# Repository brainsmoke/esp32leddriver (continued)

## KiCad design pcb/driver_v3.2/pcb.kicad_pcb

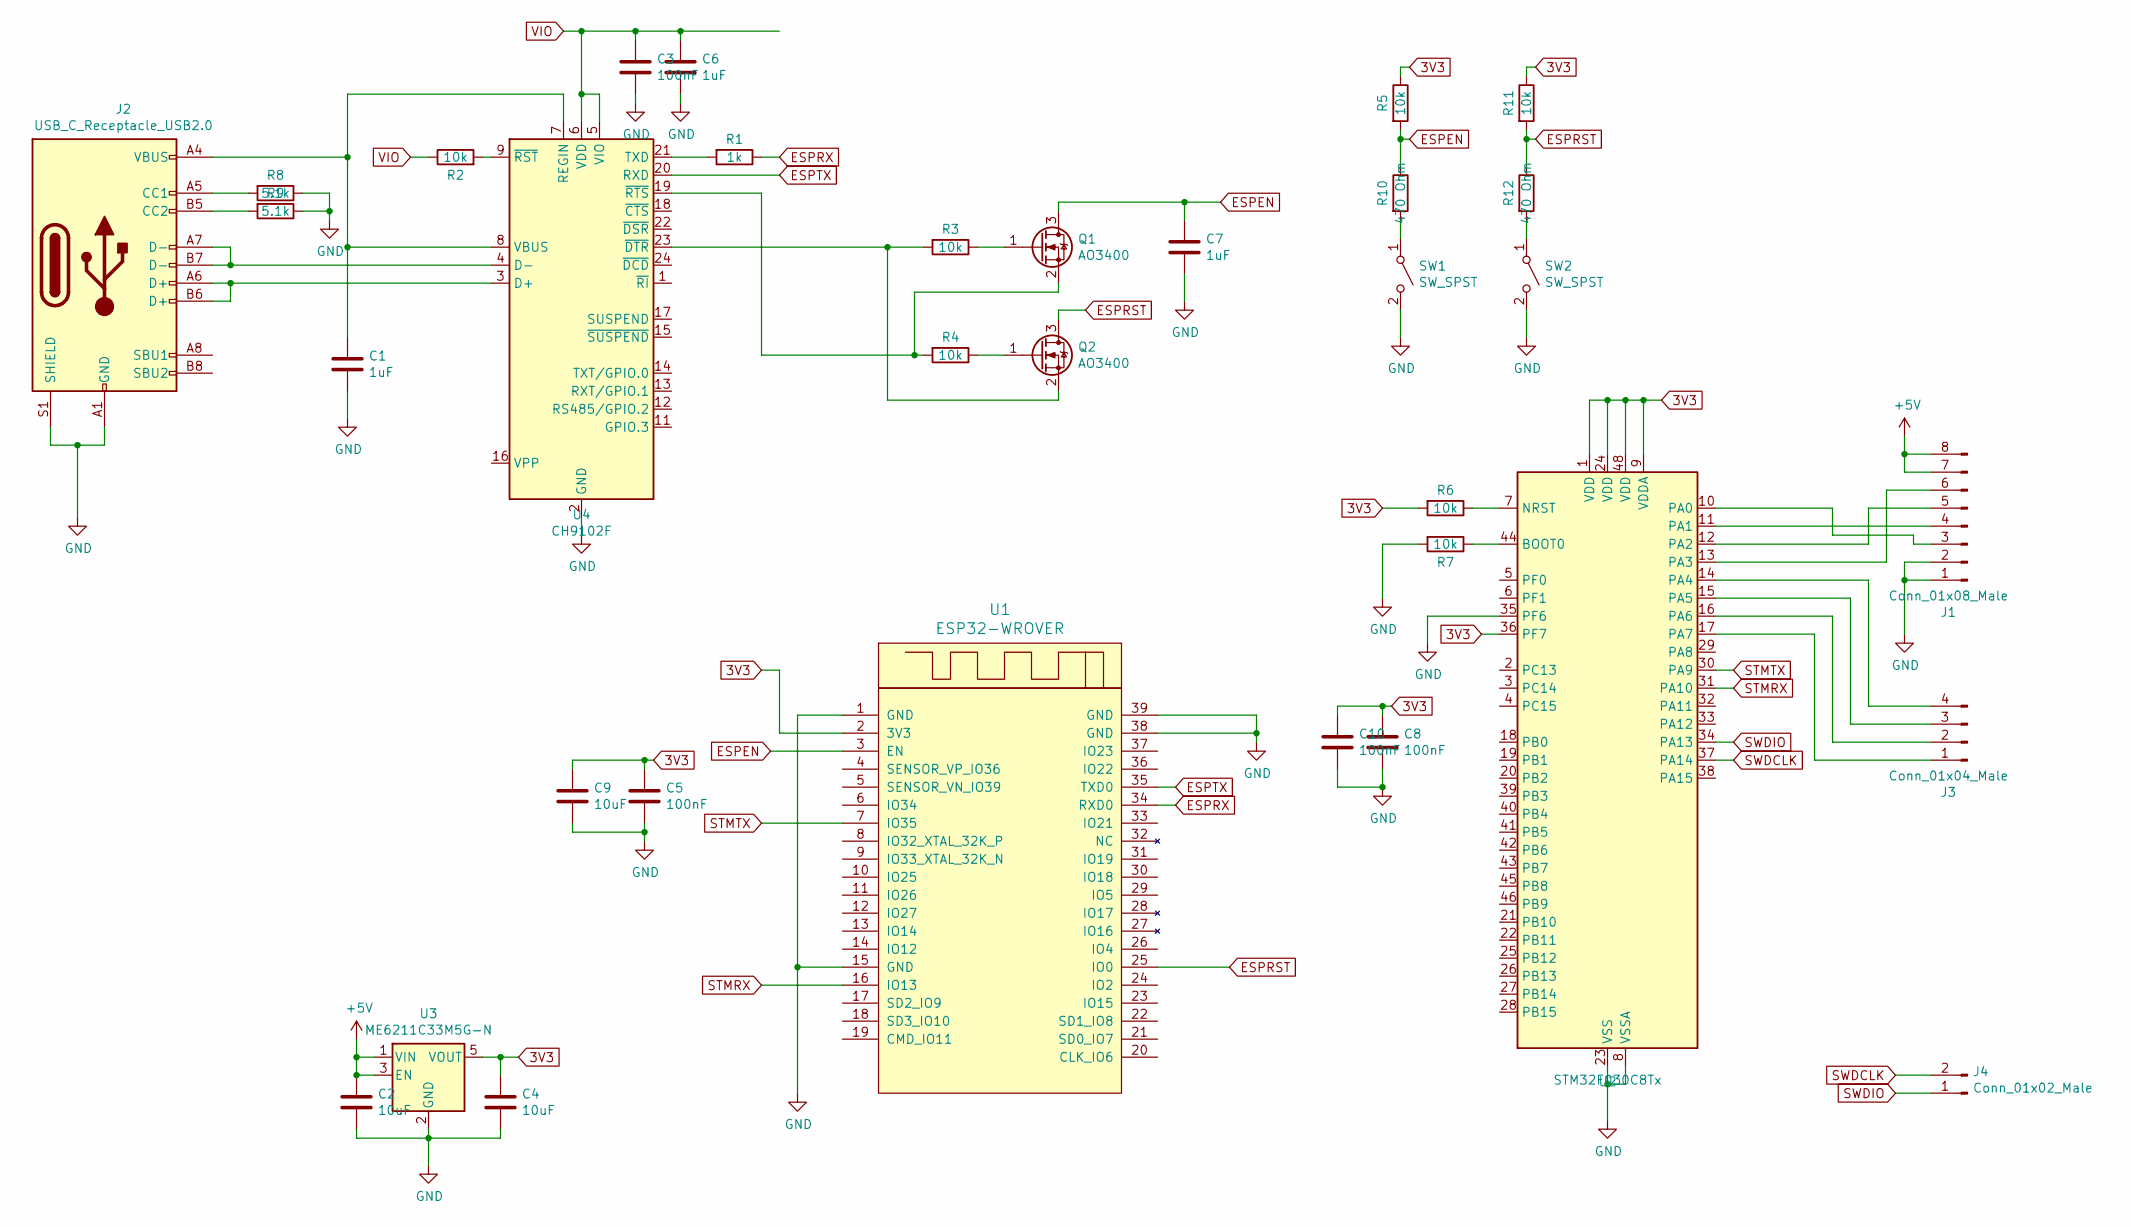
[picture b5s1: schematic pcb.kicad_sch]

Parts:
C1, C6, C7: 1uF; C_0402_1005Metric; LCSC C52923
C2, C4, C9: 10uF; C_0603_1608Metric; LCSC C19702
C3, C5, C8, C10: 100nF; C_0402_1005Metric; LCSC C1525
J1: Conn_01x08_Male; PinHeader_1x08_P2.54mm_Vertical
J2: USB_C_Receptacle_USB2.0; USB_C_Receptacle_HRO_TYPE-C-31-M-12; LCSC C165948
J3: Conn_01x04_Male; PinHeader_1x04_P2.54mm_Vertical
J4: Conn_01x02_Male; PinHeader_1x02_P2.54mm_Vertical
Q1, Q2: AO3400; SOT-23; LCSC C20917
R1: 1k; R_0402_1005Metric; LCSC C11702
R2, R3, R4, R5, R6, R7, R11: 10k; R_0402_1005Metric; LCSC C25744
R8, R9: 5.1k; R_0402_1005Metric; LCSC C25905
R10, R12: 470 Ohm; R_0402_1005Metric; LCSC C25117
SW1, SW2: SW_SPST; SW_Push_1P1T_NO_CK_KMR2; LCSC C318893
U1: ESP32-WROVER; XCVR_ESP32-WROVER
U2: STM32F030C8Tx; LQFP-48_7x7mm_P0.5mm; LCSC C23922
U3: ME6211C33M5G-N; SOT-23-5; LCSC C82942
U4: CH9102F; QFN-24-1EP_4x4mm_P0.5mm_EP2.6x2.6mm; LCSC C2858418

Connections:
3V3: C4.1, C5.1, C8.1, C9.1, C10.1, R5.1, R6.2, R11.1, U1.2 (3V3), U2.1 (VDD), U2.9 (VDDA), U2.24 (VDD), U2.36 (PF7), U2.48 (VDD), U3.5 (VOUT)
+5V: C2.1, J1.7, J1.8, U3.1 (VIN), U3.3 (EN)
ESPEN: C7.1, Q1.3 (D), R5.2, R10.1, U1.3 (EN)
ESPRST: Q2.3 (D), R11.2, R12.1, U1.25 (IO0)
ESPRX: R1.1, U1.34 (RXD0)
ESPTX: U1.35 (TXD0), U4.20 (RXD)
GND: C1.2, C2.2, C3.2, C4.2, C5.2, C6.2, C7.2, C8.2, C9.2, C10.2, J1.1, J1.2, J2.A1 (GND), J2.A12 (GND), J2.B1 (GND), J2.B12 (GND), J2.S1 (SHIELD), R7.2, R8.1, R9.1, SW1.2 (B), SW2.2 (B), U1.1 (GND), U1.15 (GND), U1.38 (GND), U1.39 (GND), U2.8 (VSSA), U2.23 (VSS), U2.35 (PF6), U2.47 (VSS), U3.2 (GND), U4.2 (GND), U4.25 (GND)
unnamed: J1.3, U2.10 (PA0)
unnamed: J1.4, U2.11 (PA1)
unnamed: J1.5, U2.12 (PA2)
unnamed: J1.6, U2.13 (PA3)
unnamed: J2.A5 (CC1), R8.2
unnamed: J2.B5 (CC2), R9.2
unnamed: J3.1, U2.17 (PA7)
unnamed: J3.2, U2.16 (PA6)
unnamed: J3.3, U2.15 (PA5)
unnamed: J3.4, U2.14 (PA4)
unnamed: Q1.1 (G), R3.1
unnamed: Q1.2 (S), R4.2, U4.19 (~RTS)
unnamed: Q2.1 (G), R4.1
unnamed: Q2.2 (S), R3.2, U4.23 (~DTR)
unnamed: R10.2, SW1.1 (A)
unnamed: R12.2, SW2.1 (A)
unnamed: R7.1, U2.44 (BOOT0)
unnamed: R6.1, U2.7 (NRST)
unnamed: J2.A6 (D+), J2.B6 (D+), U4.3 (D+)
unnamed: J2.A7 (D-), J2.B7 (D-), U4.4 (D-)
unnamed: C1.1, J2.A4 (VBUS), J2.A9 (VBUS), J2.B4 (VBUS), J2.B9 (VBUS), U4.7 (REGIN), U4.8 (VBUS)
unnamed: R1.2, U4.21 (TXD)
unnamed: R2.2, U4.9 (~RST)
STMRX: U1.16 (IO13), U2.31 (PA10)
STMTX: U1.7 (IO35), U2.30 (PA9)
SWDCLK: J4.2, U2.37 (PA14)
SWDIO: J4.1, U2.34 (PA13)
VIO: C3.1, C6.1, R2.1, U4.5 (VIO), U4.6 (VDD)

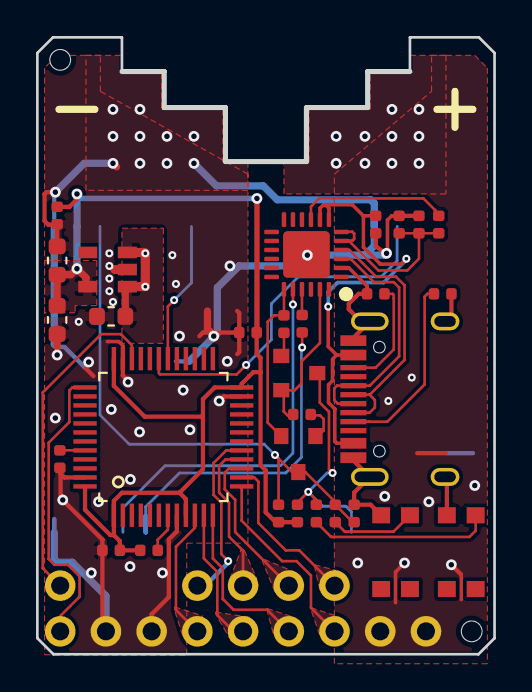
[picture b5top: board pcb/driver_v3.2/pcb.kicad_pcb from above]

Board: 4 copper layers, 25.4 x 34.3 mm, 34 parts (1 on the bottom side), 35 nets.

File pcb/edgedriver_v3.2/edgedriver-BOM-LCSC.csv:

Comment,Designator,Footprint,LCSC Part Number
"10uF","C4,C2,C9","0603","C19702"
"1uF","C7,C6,C1","0402","C52923"
"100nF","C8,C5,C3,C10","0402","C1525"
"USB_C_Receptacle_USB2.0","J2","TYPE-C-31_L8.94_W7.3","C165948"
"AO3400","Q1,Q2","SOT-23-3L","C20917"
"1k","R1","0402","C11702"
"470 Ohm","R10,R12","0402","C25167"
"10k","R6,R7,R3,R4,R5,R2,R11","0402","C25744"
"5.1k","R8,R9","0402","C25905"
"SW_SPST","SW1,SW2","Button_Switch_SMD:SW_Push_1P1T_NO_CK_KMR2","C318893"
"STM32F030C8T6","U2","LQFP-48_7.0x7.0x0.5P","C23922"
"AMS1117-3.3","U3","SOT-223","C6186"
"CH9102F","U4","QFN-24_L4.0-W4.0-P0.50EP2.8","C2858418"

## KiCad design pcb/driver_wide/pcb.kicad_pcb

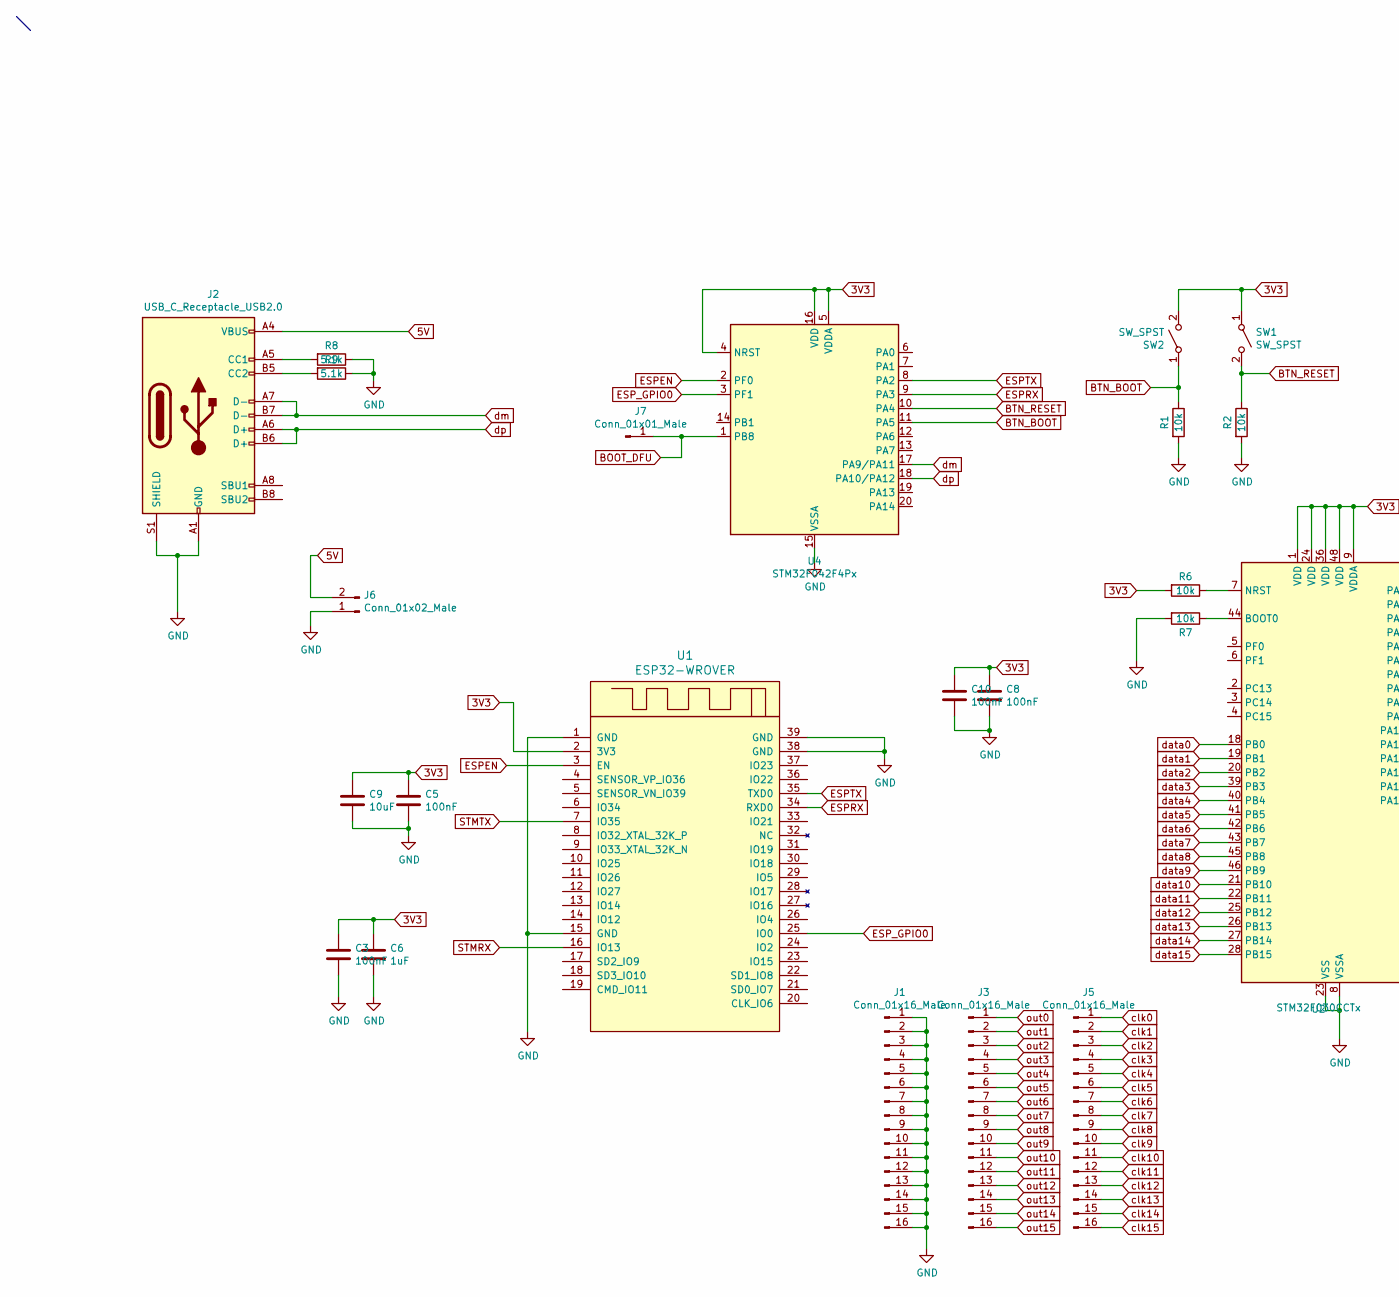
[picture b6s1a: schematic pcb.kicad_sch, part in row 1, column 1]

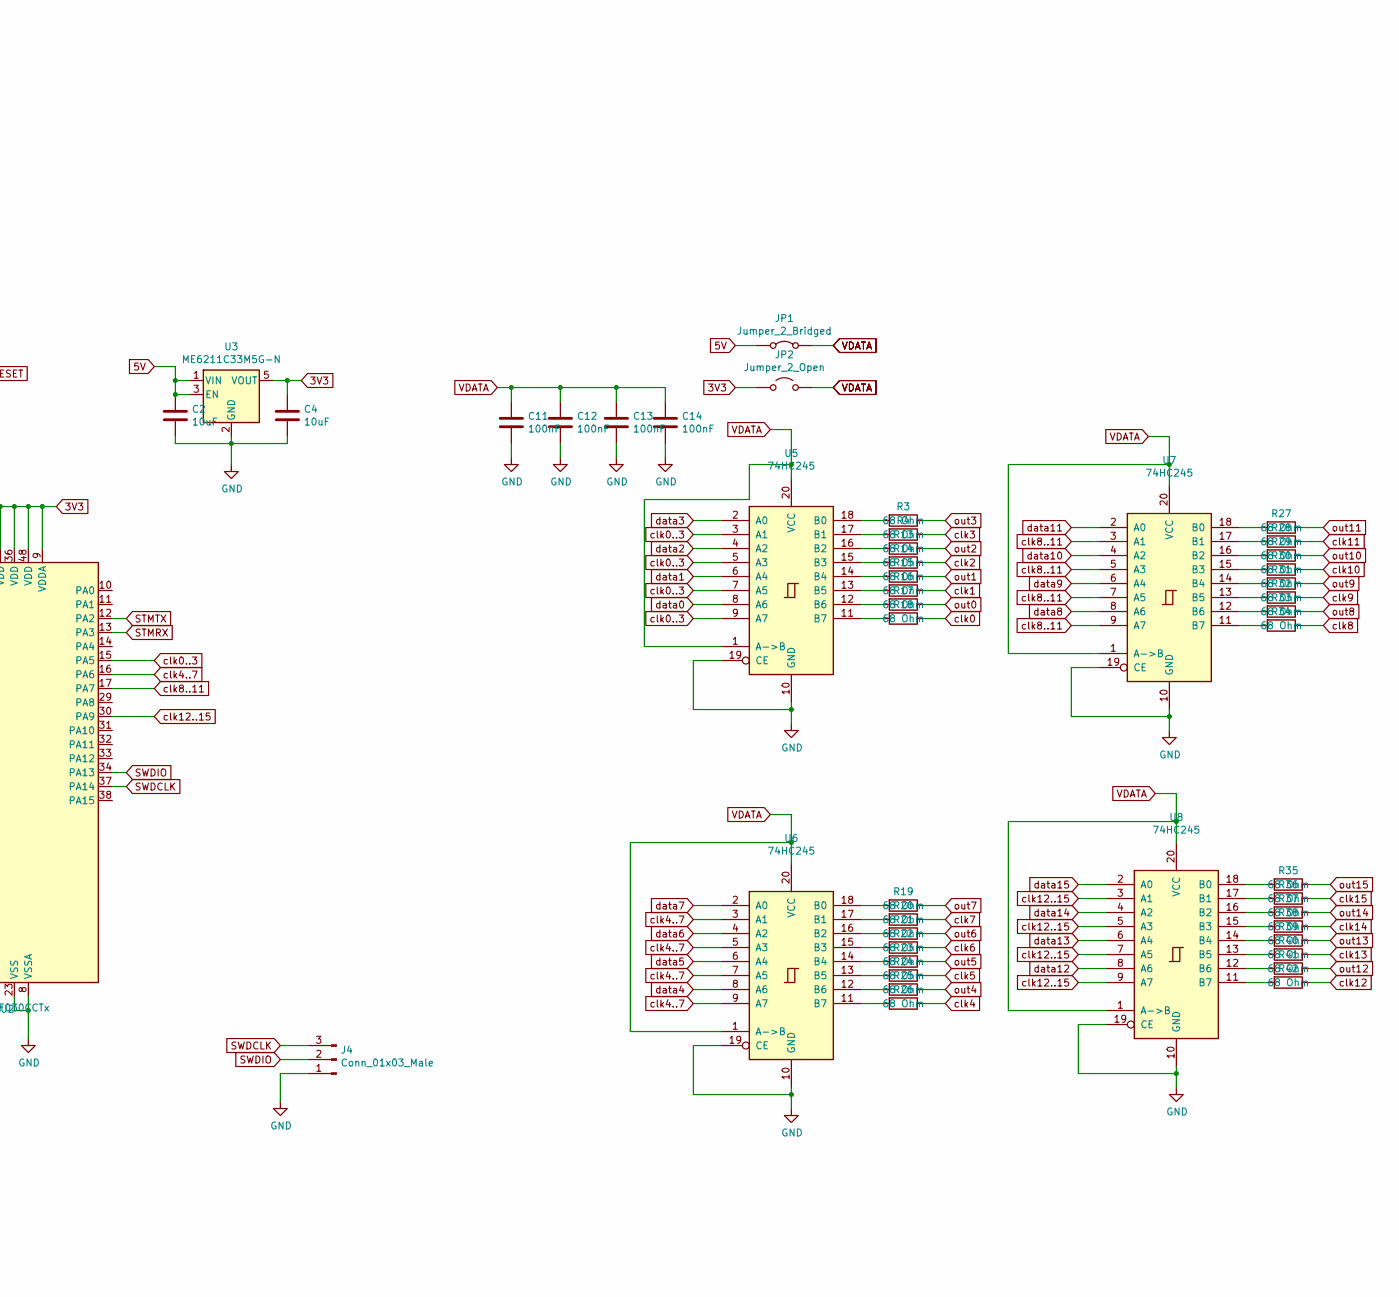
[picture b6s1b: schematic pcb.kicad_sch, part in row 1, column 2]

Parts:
C2, C4, C9: 10uF; C_0603_1608Metric; LCSC C19702
C3, C5, C8, C10: 100nF; C_0402_1005Metric; LCSC C1525
C6: 1uF; C_0402_1005Metric; LCSC C52923
C11, C12, C13, C14: 100nF; C_0402_1005Metric; LCSC C19702
J1, J3, J5: Conn_01x16_Male; PinHeader_1x16_P2.54mm_Vertical
J2: USB_C_Receptacle_USB2.0; USB_C_Receptacle_HRO_TYPE-C-31-M-12; LCSC C165948
J4: Conn_01x03_Male; PinHeader_1x03_P2.54mm_Vertical
J6: Conn_01x02_Male; PinHeader_1x02_P2.54mm_Vertical
J7: Conn_01x01_Male; PinHeader_1x01_P2.54mm_Vertical
JP1: Jumper_2_Bridged; SolderJumper-2_P1.3mm_Bridged_Pad1.0x1.5mm
JP2: Jumper_2_Open; SolderJumper-2_P1.3mm_Open_Pad1.0x1.5mm
R1, R2, R6, R7: 10k; R_0402_1005Metric; LCSC C25744
R3, R4, R13, R14, R15, R16, R17, R18, R19, R20, R21, R22, R23, R24, R25, R26, R27, R28, R29, R30, R31, R32, R33, R34, R35, R36, R37, R38, R39, R40, R41, R42: 68 Ohm; R_0402_1005Metric; LCSC C25744
R8, R9: 5.1k; R_0402_1005Metric; LCSC C25905
SW1, SW2: SW_SPST; SW_Push_1P1T_NO_CK_KMR2; LCSC C318893
U1: ESP32-WROVER; XCVR_ESP32-WROVER
U2: STM32F030CCTx; LQFP-48_7x7mm_P0.5mm
U3: ME6211C33M5G-N; SOT-23-5; LCSC C82942
U4: STM32F042F4Px; TSSOP-20_4.4x6.5mm_P0.65mm
U5, U6, U7, U8: 74HC245; TSSOP-20_4.4x6.5mm_P0.65mm

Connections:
3V3: C3.1, C4.1, C5.1, C6.1, C8.1, C9.1, C10.1, JP2.1 (A), R6.2, SW1.1 (A), SW2.2 (B), U1.2 (3V3), U2.1 (VDD), U2.9 (VDDA), U2.24 (VDD), U2.36 (VDD), U2.48 (VDD), U3.5 (VOUT), U4.4 (NRST), U4.5 (VDDA), U4.16 (VDD)
5V: C2.1, J2.A4 (VBUS), J2.A9 (VBUS), J2.B4 (VBUS), J2.B9 (VBUS), J6.2, JP1.1 (A), U3.1 (VIN), U3.3 (EN)
BOOT_DFU: J7.1, U4.1 (PB8)
BTN_BOOT: R1.1, SW2.1 (A), U4.11 (PA5)
BTN_RESET: R2.1, SW1.2 (B), U4.10 (PA4)
ESPEN: U1.3 (EN), U4.2 (PF0)
ESPRX: U1.34 (RXD0), U4.9 (PA3)
ESPTX: U1.35 (TXD0), U4.8 (PA2)
ESP_GPIO0: U1.25 (IO0), U4.3 (PF1)
GND: C2.2, C3.2, C4.2, C5.2, C6.2, C8.2, C9.2, C10.2, C11.2, C12.2, C13.2, C14.2, J1.1, J1.2, J1.3, J1.4, J1.5, J1.6, J1.7, J1.8, J1.9, J1.10, J1.11, J1.12, J1.13, J1.14, J1.15, J1.16, J2.A1 (GND), J2.A12 (GND), J2.B1 (GND), J2.B12 (GND), J2.S1 (SHIELD), J4.1, J6.1, R1.2, R2.2, R7.2, R8.1, R9.1, U1.1 (GND), U1.15 (GND), U1.38 (GND), U1.39 (GND), U2.8 (VSSA), U2.23 (VSS), U2.35 (VSS), U2.47 (VSS), U3.2 (GND), U4.15 (VSSA), U5.10 (GND), U5.19 (CE), U6.10 (GND), U6.19 (CE), U7.10 (GND), U7.19 (CE), U8.10 (GND), U8.19 (CE)
unnamed: J2.A5 (CC1), R8.2
unnamed: J2.B5 (CC2), R9.2
unnamed: R7.1, U2.44 (BOOT0)
unnamed: R6.1, U2.7 (NRST)
unnamed: R3.2, U5.18 (B0)
unnamed: R4.2, U5.17 (B1)
unnamed: R13.2, U5.16 (B2)
unnamed: R14.2, U5.15 (B3)
unnamed: R15.2, U5.14 (B4)
unnamed: R16.2, U5.13 (B5)
unnamed: R17.2, U5.12 (B6)
unnamed: R18.2, U5.11 (B7)
unnamed: R19.2, U6.18 (B0)
unnamed: R20.2, U6.17 (B1)
unnamed: R21.2, U6.16 (B2)
unnamed: R22.2, U6.15 (B3)
unnamed: R23.2, U6.14 (B4)
unnamed: R24.2, U6.13 (B5)
unnamed: R25.2, U6.12 (B6)
unnamed: R26.2, U6.11 (B7)
unnamed: R27.2, U7.18 (B0)
unnamed: R28.2, U7.17 (B1)
unnamed: R29.2, U7.16 (B2)
unnamed: R30.2, U7.15 (B3)
unnamed: R31.2, U7.14 (B4)
unnamed: R32.2, U7.13 (B5)
unnamed: R33.2, U7.12 (B6)
unnamed: R34.2, U7.11 (B7)
unnamed: R35.2, U8.18 (B0)
unnamed: R36.2, U8.17 (B1)
unnamed: R37.2, U8.16 (B2)
unnamed: R38.2, U8.15 (B3)
unnamed: R39.2, U8.14 (B4)
unnamed: R40.2, U8.13 (B5)
unnamed: R41.2, U8.12 (B6)
unnamed: R42.2, U8.11 (B7)
STMRX: U1.16 (IO13), U2.13 (PA3)
STMTX: U1.7 (IO35), U2.12 (PA2)
SWDCLK: J4.3, U2.37 (PA14)
SWDIO: J4.2, U2.34 (PA13)
VDATA: C11.1, C12.1, C13.1, C14.1, JP1.2 (B), JP2.2 (B), U5.1 (A->B), U5.20 (VCC), U6.1 (A->B), U6.20 (VCC), U7.1 (A->B), U7.20 (VCC), U8.1 (A->B), U8.20 (VCC)
clk0: J5.1, R18.1
clk0..3: U2.15 (PA5), U5.3 (A1), U5.5 (A3), U5.7 (A5), U5.9 (A7)
clk1: J5.2, R16.1
clk2: J5.3, R14.1
clk3: J5.4, R4.1
clk4: J5.5, R26.1
clk4..7: U2.16 (PA6), U6.3 (A1), U6.5 (A3), U6.7 (A5), U6.9 (A7)
clk5: J5.6, R24.1
clk6: J5.7, R22.1
clk7: J5.8, R20.1
clk8: J5.9, R34.1
clk8..11: U2.17 (PA7), U7.3 (A1), U7.5 (A3), U7.7 (A5), U7.9 (A7)
clk9: J5.10, R32.1
clk10: J5.11, R30.1
clk11: J5.12, R28.1
clk12: J5.13, R42.1
clk12..15: U2.30 (PA9), U8.3 (A1), U8.5 (A3), U8.7 (A5), U8.9 (A7)
clk13: J5.14, R40.1
clk14: J5.15, R38.1
clk15: J5.16, R36.1
data0: U2.18 (PB0), U5.8 (A6)
data1: U2.19 (PB1), U5.6 (A4)
data2: U2.20 (PB2), U5.4 (A2)
data3: U2.39 (PB3), U5.2 (A0)
data4: U2.40 (PB4), U6.8 (A6)
data5: U2.41 (PB5), U6.6 (A4)
data6: U2.42 (PB6), U6.4 (A2)
data7: U2.43 (PB7), U6.2 (A0)
data8: U2.45 (PB8), U7.8 (A6)
data9: U2.46 (PB9), U7.6 (A4)
data10: U2.21 (PB10), U7.4 (A2)
data11: U2.22 (PB11), U7.2 (A0)
data12: U2.25 (PB12), U8.8 (A6)
data13: U2.26 (PB13), U8.6 (A4)
data14: U2.27 (PB14), U8.4 (A2)
data15: U2.28 (PB15), U8.2 (A0)
dm: J2.A7 (D-), J2.B7 (D-), U4.17 (PA9/PA11)
dp: J2.A6 (D+), J2.B6 (D+), U4.18 (PA10/PA12)
out0: J3.1, R17.1
out1: J3.2, R15.1
out2: J3.3, R13.1
out3: J3.4, R3.1
out4: J3.5, R25.1
out5: J3.6, R23.1
out6: J3.7, R21.1
out7: J3.8, R19.1
out8: J3.9, R33.1
out9: J3.10, R31.1
out10: J3.11, R29.1
out11: J3.12, R27.1
out12: J3.13, R41.1
out13: J3.14, R39.1
out14: J3.15, R37.1
out15: J3.16, R35.1

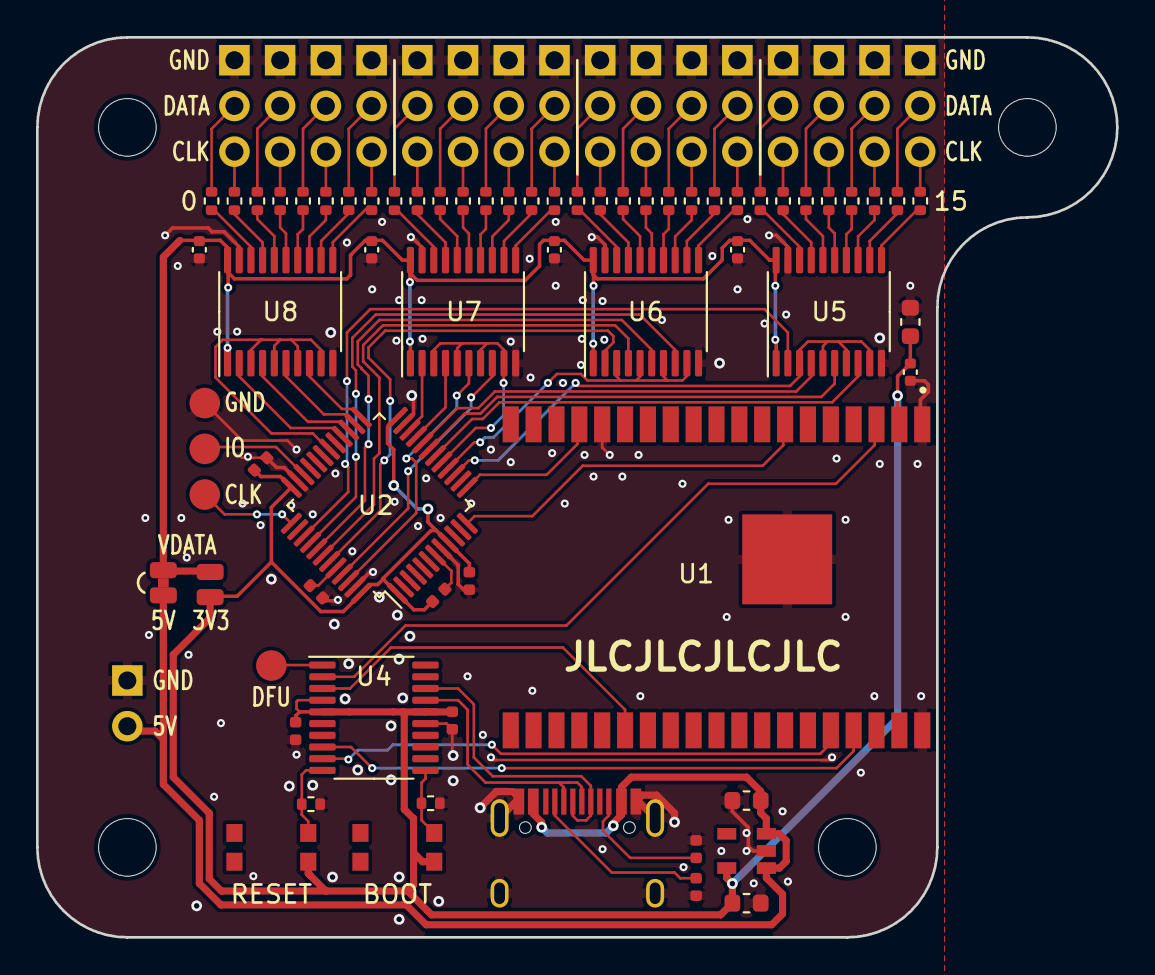
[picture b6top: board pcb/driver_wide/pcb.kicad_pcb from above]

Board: 2 copper layers, 60.0 x 50.0 mm, 69 parts (0 on the bottom side), 105 nets.

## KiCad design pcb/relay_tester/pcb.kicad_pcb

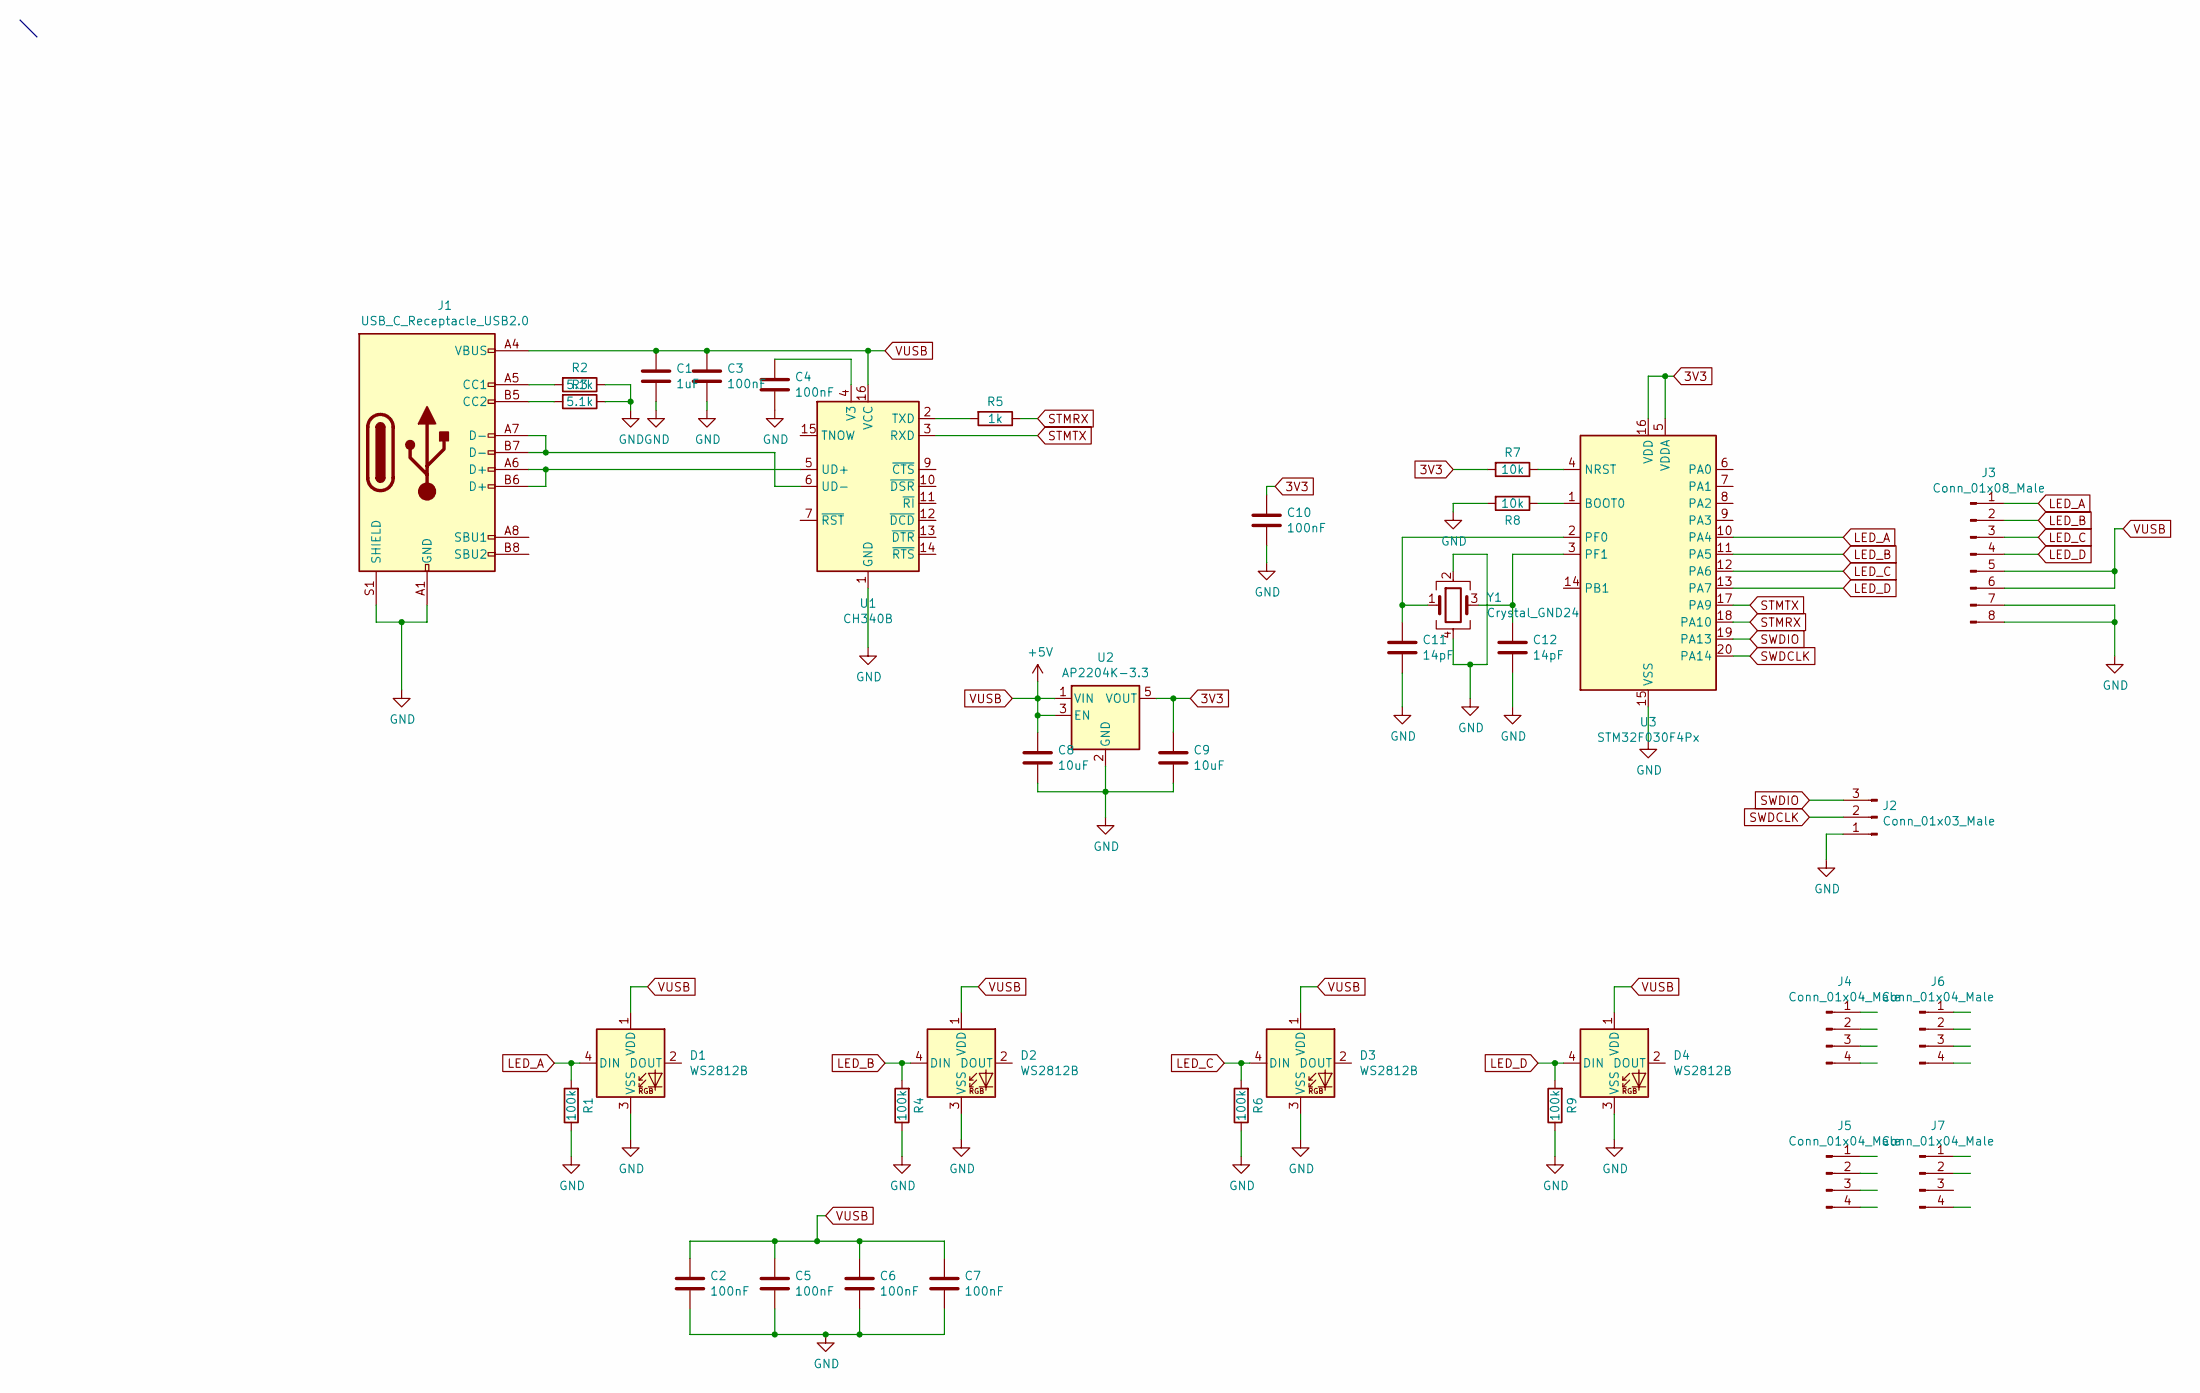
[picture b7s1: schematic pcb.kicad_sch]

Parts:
C1: 1uF; C_0603_1608Metric_Pad1.08x0.95mm_HandSolder; LCSC C52923
C2, C3, C4, C5, C6, C7, C10: 100nF; C_0603_1608Metric_Pad1.08x0.95mm_HandSolder; LCSC C1525
C8, C9: 10uF; C_0603_1608Metric_Pad1.08x0.95mm_HandSolder; LCSC C19702
C11, C12: 14pF; C_0603_1608Metric_Pad1.08x0.95mm_HandSolder; LCSC C19702
D1, D2, D3, D4: WS2812B; LED_WS2812B_PLCC4_5.0x5.0mm_P3.2mm
J1: USB_C_Receptacle_USB2.0; USB_C_Receptacle_HRO_TYPE-C-31-M-12
J2: Conn_01x03_Male; PinHeader_1x03_P2.54mm_Vertical
J3: Conn_01x08_Male; padauk_test_a
J4, J5, J6, J7: Conn_01x04_Male; PinHeader_1x04_P2.54mm_Vertical
R1, R4, R6, R9: 100k; R_0603_1608Metric_Pad0.98x0.95mm_HandSolder; LCSC C11702
R2, R3: 5.1k; R_0603_1608Metric_Pad0.98x0.95mm_HandSolder; LCSC C25905
R5: 1k; R_0603_1608Metric_Pad0.98x0.95mm_HandSolder; LCSC C11702
R7, R8: 10k; R_0603_1608Metric_Pad0.98x0.95mm_HandSolder; LCSC C25744
U1: CH340B; SOIC-16_3.9x9.9mm_P1.27mm
U2: AP2204K-3.3; SOT-23-5
U3: STM32F030F4Px; TSSOP-20_4.4x6.5mm_P0.65mm
Y1: Crystal_GND24; TSX-3225

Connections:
3V3: C9.1, C10.1, R7.2, U2.5 (VOUT), U3.5 (VDDA), U3.16 (VDD)
GND: C1.2, C2.2, C3.2, C4.2, C5.2, C6.2, C7.2, C8.2, C9.2, C10.2, C11.2, C12.2, D1.3 (VSS), D2.3 (VSS), D3.3 (VSS), D4.3 (VSS), J1.A1 (GND), J1.A12 (GND), J1.B1 (GND), J1.B12 (GND), J1.S1 (SHIELD), J2.1, J3.7, J3.8, R1.1, R2.1, R3.1, R4.1, R6.1, R8.2, R9.1, U1.1 (GND), U2.2 (GND), U3.15 (VSS), Y1.2, Y1.4
LED_A: D1.4 (DIN), J3.1, R1.2, U3.10 (PA4)
LED_B: D2.4 (DIN), J3.2, R4.2, U3.11 (PA5)
LED_C: D3.4 (DIN), J3.3, R6.2, U3.12 (PA6)
LED_D: D4.4 (DIN), J3.4, R9.2, U3.13 (PA7)
unnamed: J1.A5 (CC1), R2.2
unnamed: J1.B5 (CC2), R3.2
unnamed: R5.2, U1.2 (TXD)
unnamed: J1.A6 (D+), J1.B6 (D+), U1.5 (UD+)
unnamed: J1.A7 (D-), J1.B7 (D-), U1.6 (UD-)
unnamed: C4.1, U1.4 (V3)
unnamed: R8.1, U3.1 (BOOT0)
unnamed: R7.1, U3.4 (NRST)
unnamed: C11.1, U3.2 (PF0), Y1.1
unnamed: C12.1, U3.3 (PF1), Y1.3
STMRX: R5.1, U3.18 (PA10)
STMTX: U1.3 (RXD), U3.17 (PA9)
SWDCLK: J2.2, U3.20 (PA14)
SWDIO: J2.3, U3.19 (PA13)
VUSB: C1.1, C2.1, C3.1, C5.1, C6.1, C7.1, C8.1, D1.1 (VDD), D2.1 (VDD), D3.1 (VDD), D4.1 (VDD), J1.A4 (VBUS), J1.A9 (VBUS), J1.B4 (VBUS), J1.B9 (VBUS), J3.5, J3.6, U1.16 (VCC), U2.1 (VIN), U2.3 (EN)

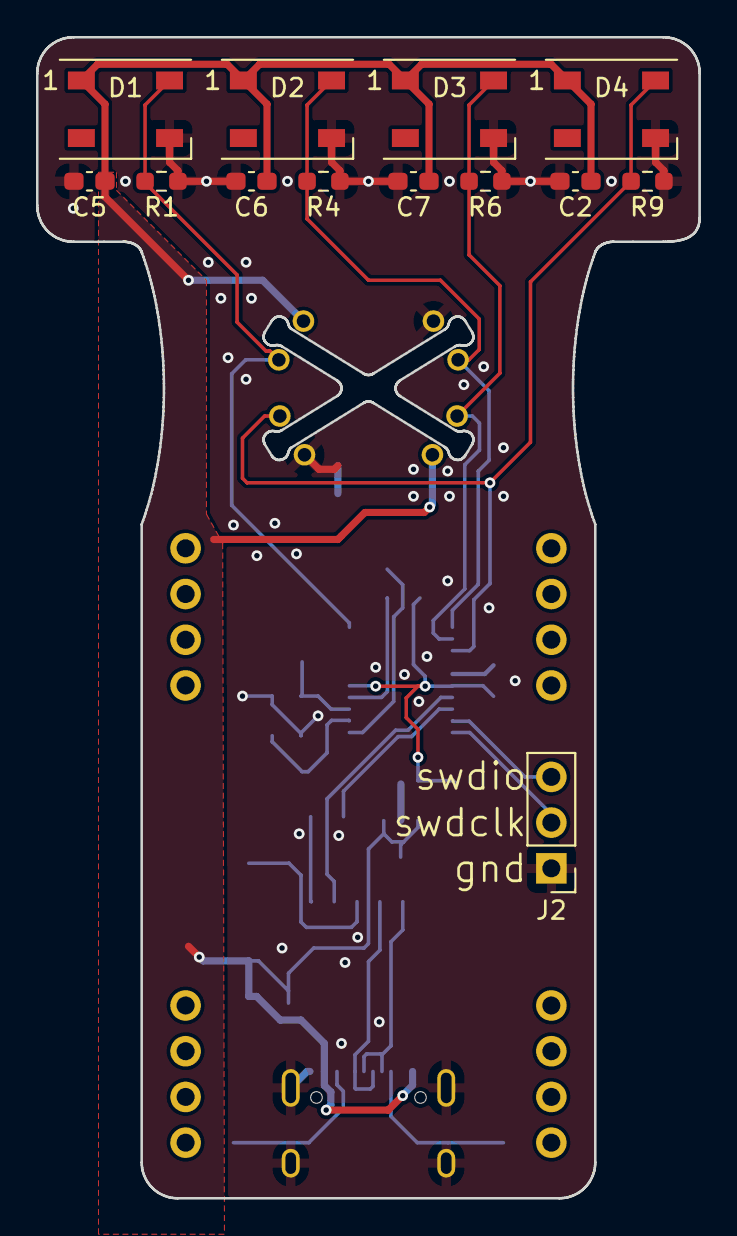
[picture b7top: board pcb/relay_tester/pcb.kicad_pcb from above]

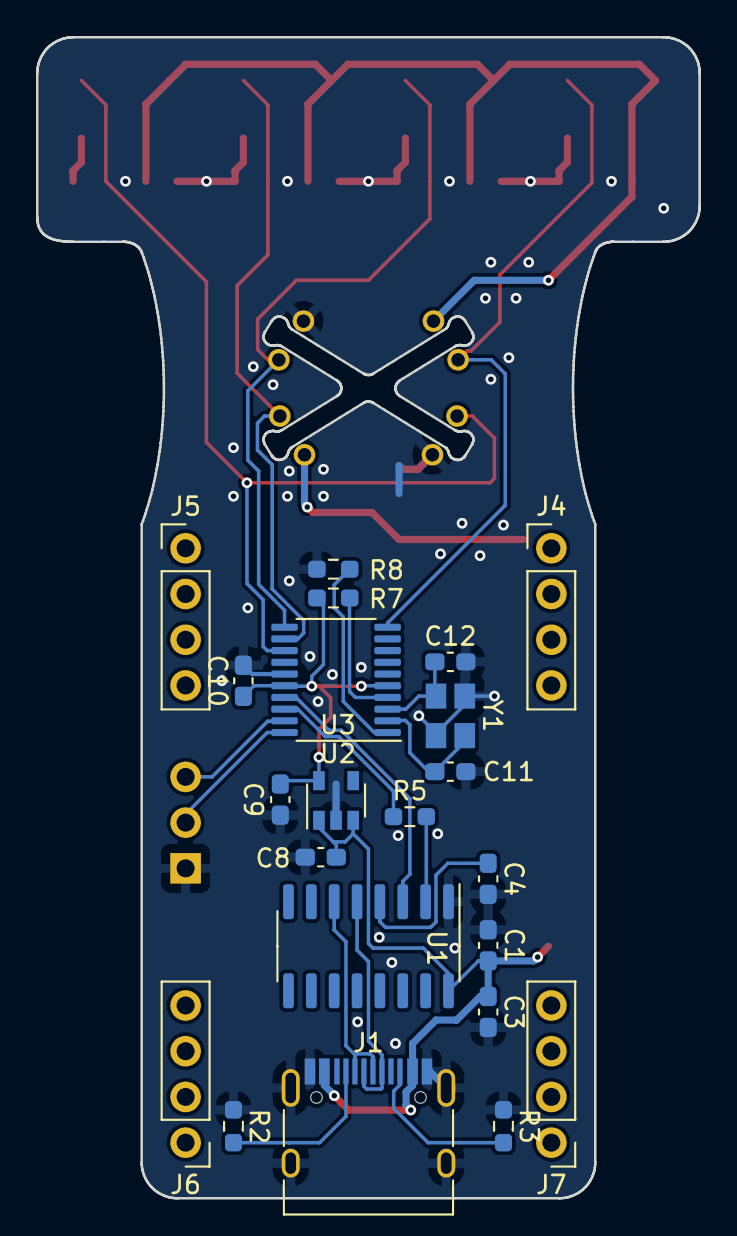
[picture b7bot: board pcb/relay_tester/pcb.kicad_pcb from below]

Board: 2 copper layers, 36.8 x 64.5 mm, 36 parts (22 on the bottom side), 21 nets.
